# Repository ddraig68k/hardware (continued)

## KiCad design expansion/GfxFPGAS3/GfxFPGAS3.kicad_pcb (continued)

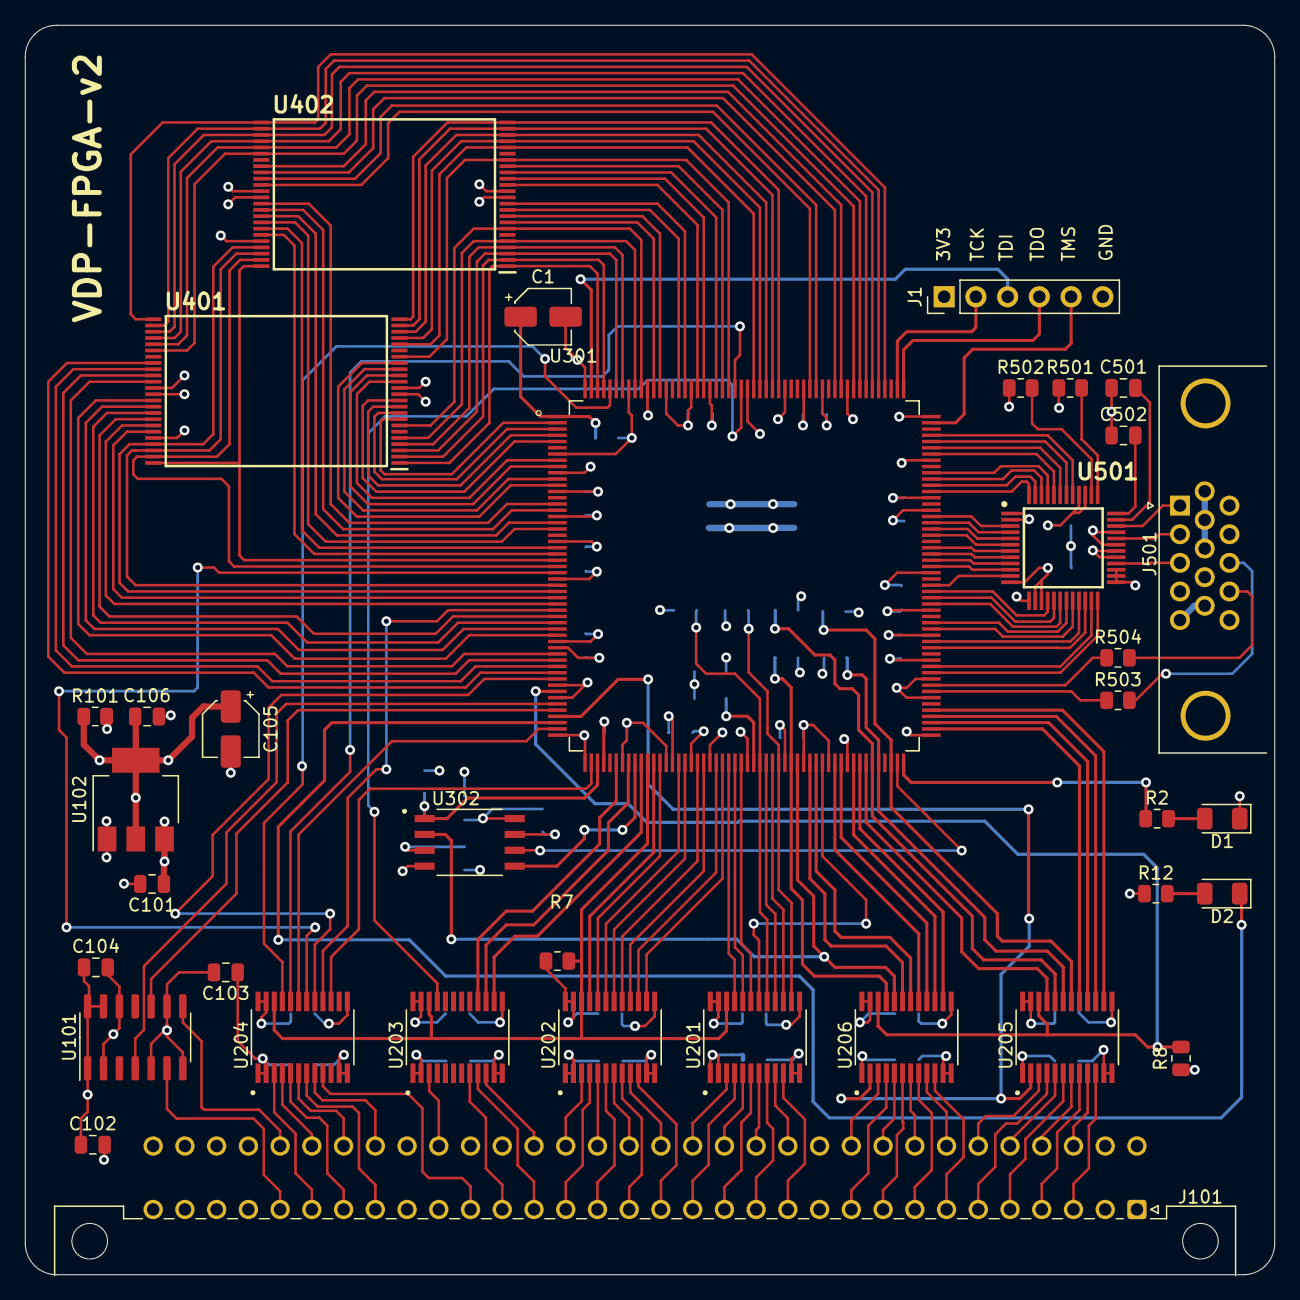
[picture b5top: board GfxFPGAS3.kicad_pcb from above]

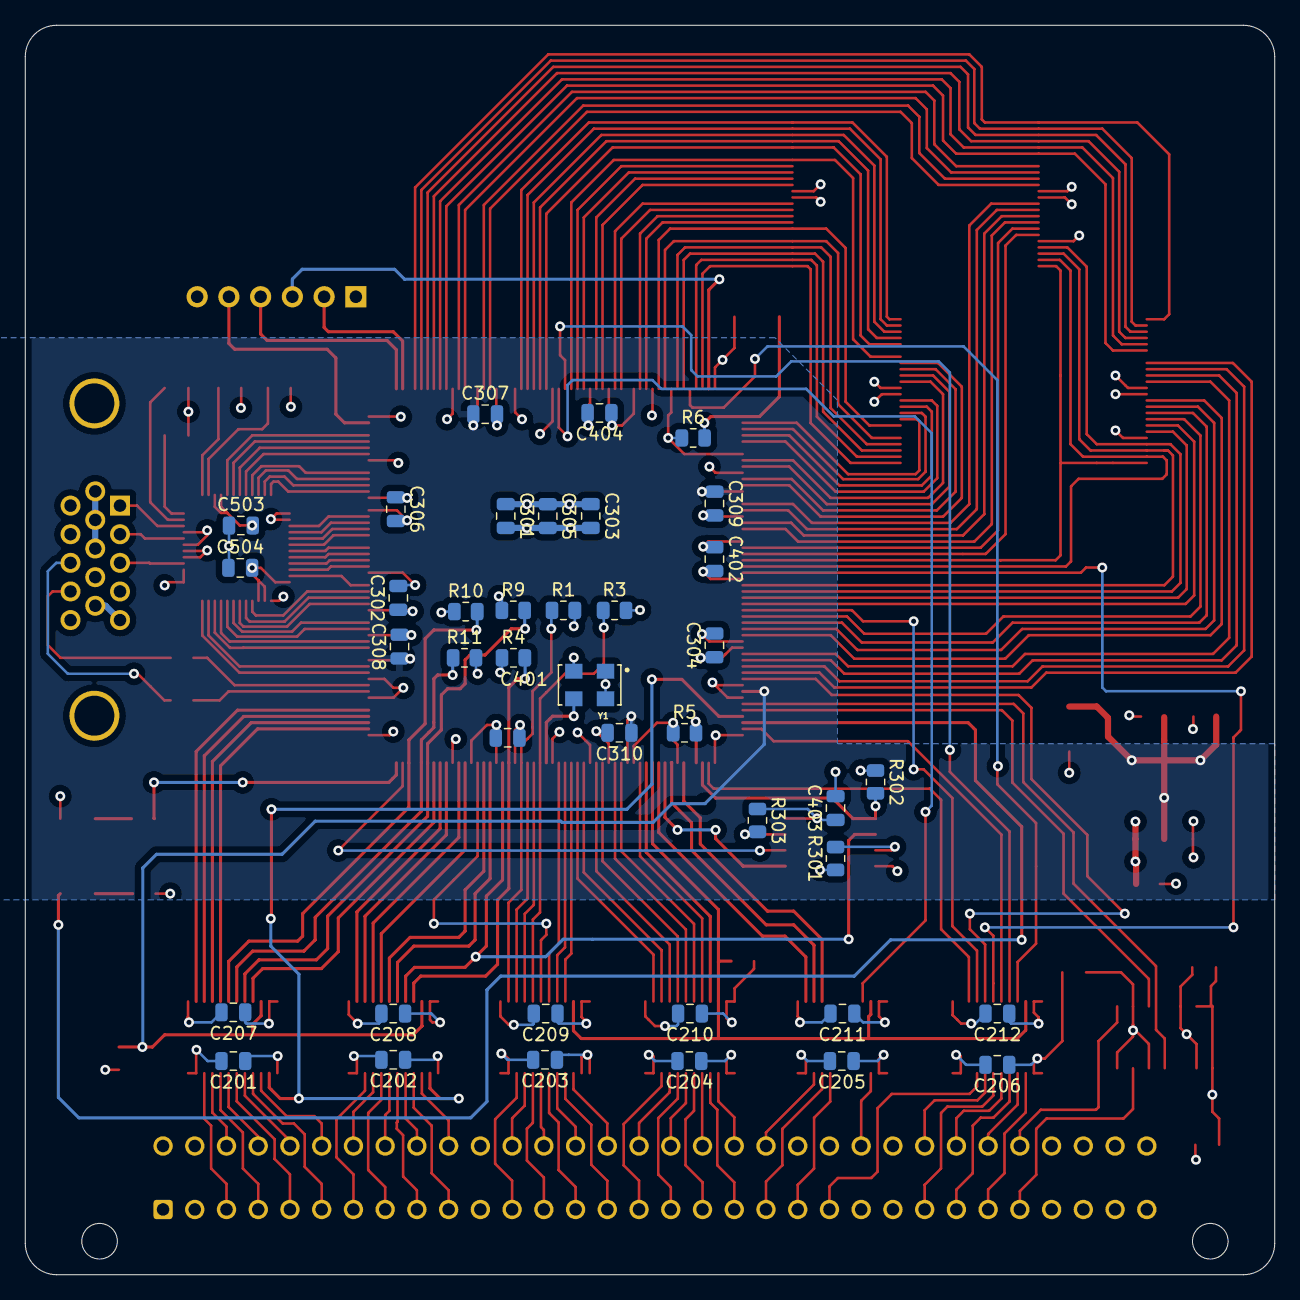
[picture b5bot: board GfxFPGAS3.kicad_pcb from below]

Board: 4 copper layers, 100.0 x 100.0 mm, 76 parts (40 on the bottom side), 208 nets.
